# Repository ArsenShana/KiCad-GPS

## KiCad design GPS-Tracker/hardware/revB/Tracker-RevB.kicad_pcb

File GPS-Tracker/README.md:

# GPS Tracker — демонстрационный прототип

Открыть симуляцию: `python3 server.py`, затем http://127.0.0.1:8765 . Презентация: http://127.0.0.1:8765/presentation.html .

Сборка ядра на macOS: `clang++ -std=c++17 -dynamiclib firmware/tracker.cpp -o firmware/libtracker.dylib`.
Проверка: `python3 firmware/test_core.py`.

KiCad: hardware/GPS-Tracker.kicad_pro. Плата — 70 × 45 мм, блоковая компоновка с условными габаритами модулей. Отсутствуют электрические соединения и реальные посадочные места; изготовление по этим файлам недопустимо. Схема — функциональная, а не электрическая.

Результат: работающая локальная симуляция исполняет C++ ядро; 3D модель компоновки, схема обмена, протокол, презентация. Не реализованы физические UART/BLE/LTE драйверы, загрузочный образ, телефонное приложение и production сервер. Локальный сервер обслуживает симуляцию, не является сервером приёма реальных устройств. Модель не оценивает RF, точность GPS, энергопотребление или срок работы батареи.

До выпуска: согласовать операторов/страны, наличие LTE-M/NB-IoT, GNSS выбранного варианта BG95, eUICC и профили оператора, размеры, аккумулятор и срок работы, сервер и приложение Android/iOS. eSIM не создаёт покрытие; телефон помогает только при собственном интернете. См. docs/architecture.md.

## Ревизия B

Улучшенный инженерный черновик: hardware/revB/Tracker-RevB.kicad_pro. Конкретные компоненты, именованные цепи и PCB без трассировки. См. hardware/revB/review.md, BOM.csv, ERC.json и DRC.json. Ревизия не готова к производству.

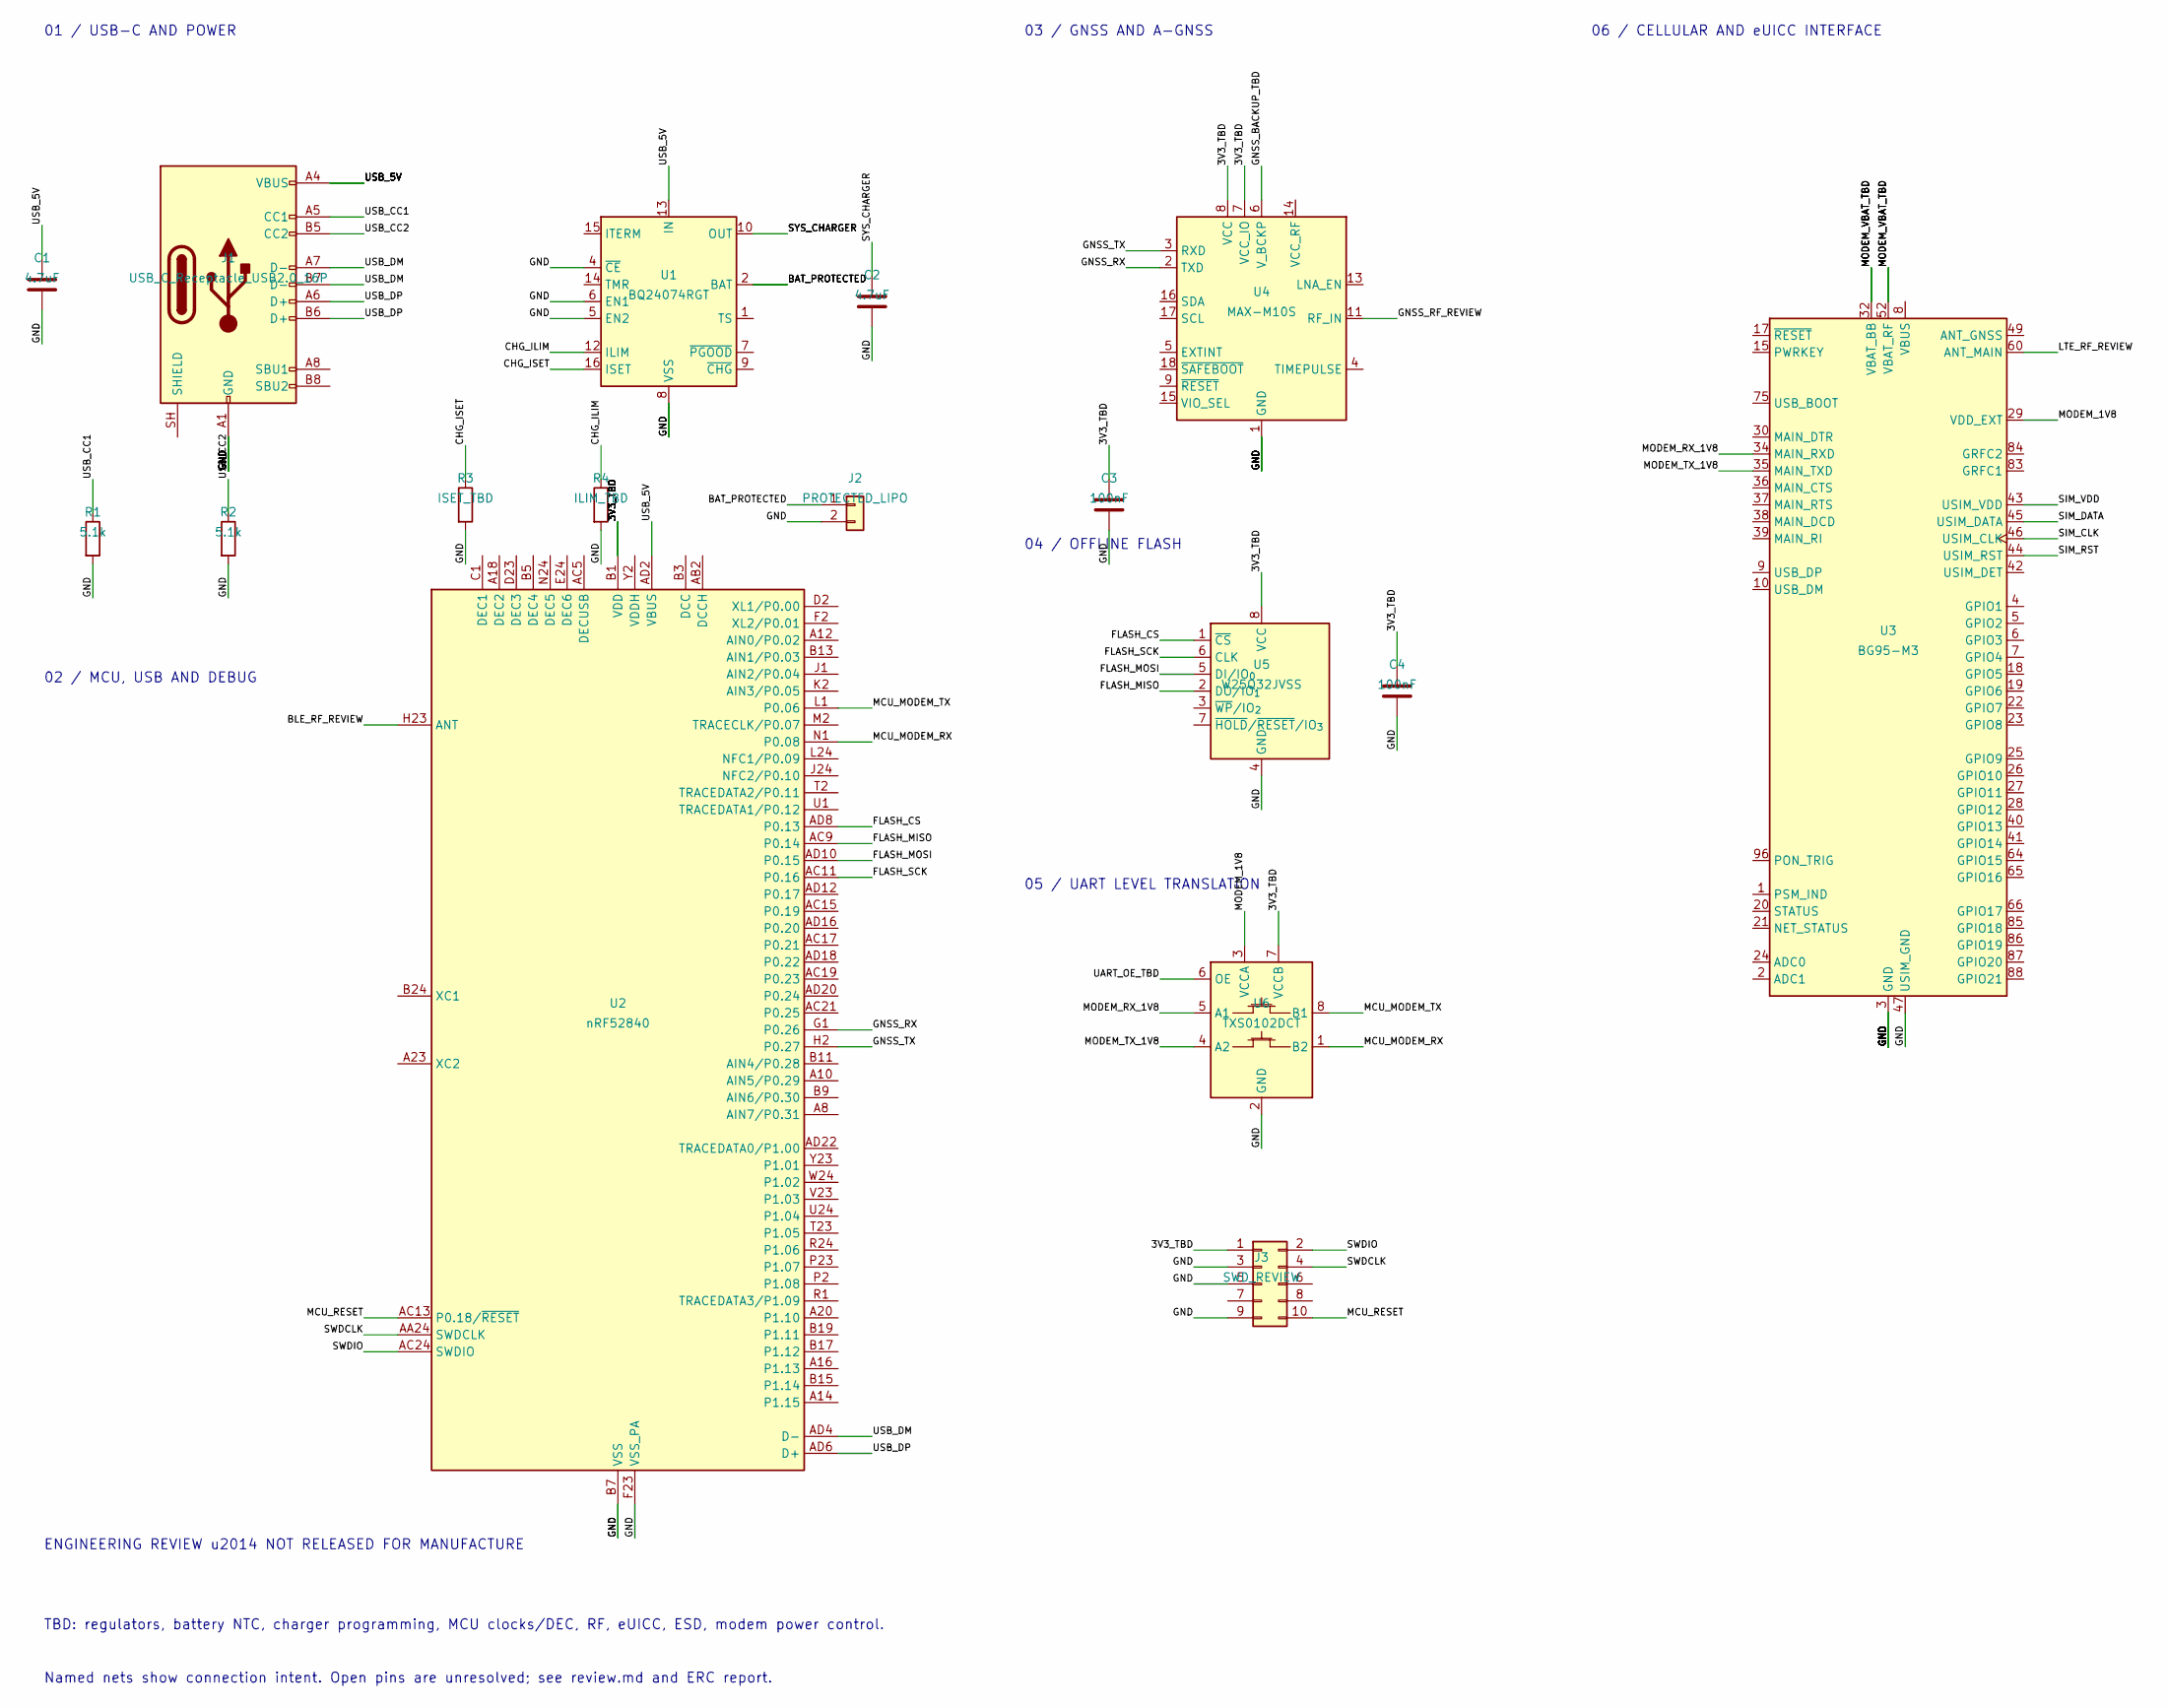
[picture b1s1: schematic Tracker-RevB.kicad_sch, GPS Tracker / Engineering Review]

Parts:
C1, C2: 4.7uF; C_0603_1608Metric
C3, C4: 100nF; C_0603_1608Metric
J1: USB_C_Receptacle_USB2.0_16P; USB_C_Receptacle_GCT_USB4105-xx-A_16P_TopMnt_Horizontal
J2: PROTECTED_LIPO; JST_PH_B2B-PH-K_1x02_P2.00mm_Vertical
J3: SWD_REVIEW; PinHeader_2x05_P1.27mm_Vertical
R1, R2: 5.1k; R_0603_1608Metric
R3: ISET_TBD; R_0603_1608Metric
R4: ILIM_TBD; R_0603_1608Metric
U1: BQ24074RGT; VQFN-16-1EP_3x3mm_P0.5mm_EP1.6x1.6mm
U2: nRF52840; Nordic_AQFN-73-1EP_7x7mm_P0.5mm
U3: BG95-M3; Quectel_BG95
U4: MAX-M10S; ublox_MAX
U5: W25Q32JVSS; SOIC-8_5.3x5.3mm_P1.27mm
U6: TXS0102DCT; SSOP-8_2.95x2.8mm_P0.65mm

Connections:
/3V3_TBD: C3.1, C4.1, J3.1, U2.A22 (VDD), U2.AD14 (VDD), U2.AD23 (VDD), U2.B1 (VDD), U2.W1 (VDD), U4.7 (VCC_IO), U4.8 (VCC), U5.8 (VCC), U6.7 (VCCB)
/BAT_PROTECTED: J2.1, U1.2 (BAT), U1.3 (BAT)
/BLE_RF_REVIEW: U2.H23 (ANT)
/CHG_ILIM: R4.1, U1.12 (ILIM)
/CHG_ISET: R3.1, U1.16 (ISET)
/FLASH_CS: U2.AD8 (P0.13), U5.1 (~CS)
/FLASH_MISO: U2.AC9 (P0.14), U5.2 (DO/IO_{1})
/FLASH_MOSI: U2.AD10 (P0.15), U5.5 (DI/IO_{0})
/FLASH_SCK: U2.AC11 (P0.16), U5.6 (CLK)
/GND: C1.2, C2.2, C3.2, C4.2, J1.A1 (GND), J1.A12 (GND), J1.B1 (GND), J1.B12 (GND), J2.2, J3.3, J3.5, J3.9, R1.2, R2.2, R3.2, R4.2, U1.4 (~CE), U1.5 (EN2), U1.6 (EN1), U1.8 (VSS), U1.17 (VSS), U2.B7 (VSS), U2.EP (VSS), U2.F23 (VSS_PA), U3.3 (GND), U3.31 (GND), U3.47 (USIM_GND), U3.48 (GND), U3.50 (GND), U3.54 (GND), U3.55 (GND), U3.58 (GND), U3.59 (GND), U3.61 (GND), U3.62 (GND), U3.67 (GND), U3.68 (GND), U3.69 (GND), U3.70 (GND), U3.71 (GND), U3.72 (GND), U3.73 (GND), U3.74 (GND), U3.79 (GND), U3.80 (GND), U3.81 (GND), U3.82 (GND), U3.89 (GND), U3.90 (GND), U3.91 (GND), U3.100 (GND), U3.101 (GND), U3.102 (GND), U4.1 (GND), U4.10 (GND), U4.12 (GND), U5.4 (GND), U6.2 (GND)
/GNSS_BACKUP_TBD: U4.6 (V_BCKP)
/GNSS_RF_REVIEW: U4.11 (RF_IN)
/GNSS_RX: U2.G1 (P0.26), U4.2 (TXD)
/GNSS_TX: U2.H2 (P0.27), U4.3 (RXD)
/LTE_RF_REVIEW: U3.60 (ANT_MAIN)
/MCU_MODEM_RX: U2.N1 (P0.08), U6.1 (B2)
/MCU_MODEM_TX: U2.L1 (P0.06), U6.8 (B1)
/MCU_RESET: J3.10, U2.AC13 (P0.18/~RESET)
/MODEM_1V8: U3.29 (VDD_EXT), U6.3 (VCCA)
/MODEM_RX_1V8: U3.34 (MAIN_RXD), U6.5 (A1)
/MODEM_TX_1V8: U3.35 (MAIN_TXD), U6.4 (A2)
/MODEM_VBAT_TBD: U3.32 (VBAT_BB), U3.33 (VBAT_BB), U3.52 (VBAT_RF), U3.53 (VBAT_RF)
/SIM_CLK: U3.46 (USIM_CLK)
/SIM_DATA: U3.45 (USIM_DATA)
/SIM_RST: U3.44 (USIM_RST)
/SIM_VDD: U3.43 (USIM_VDD)
/SWDCLK: J3.4, U2.AA24 (SWDCLK)
/SWDIO: J3.2, U2.AC24 (SWDIO)
/SYS_CHARGER: C2.1, U1.10 (OUT), U1.11 (OUT)
/UART_OE_TBD: U6.6 (OE)
/USB_5V: C1.1, J1.A4 (VBUS), J1.A9 (VBUS), J1.B4 (VBUS), J1.B9 (VBUS), U1.13 (IN), U2.AD2 (VBUS)
/USB_CC1: J1.A5 (CC1), R1.1
/USB_CC2: J1.B5 (CC2), R2.1
/USB_DM: J1.A7 (D-), J1.B7 (D-), U2.AD4 (D-)
/USB_DP: J1.A6 (D+), J1.B6 (D+), U2.AD6 (D+)

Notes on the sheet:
01 / USB-C AND POWER
02 / MCU, USB AND DEBUG
03 / GNSS AND A-GNSS
04 / OFFLINE FLASH
05 / UART LEVEL TRANSLATION
06 / CELLULAR AND eUICC INTERFACE
ENGINEERING REVIEW u2014 NOT RELEASED FOR MANUFACTURE
TBD: regulators, battery NTC, charger programming, MCU clocks/DEC, RF, eUICC, ESD, modem power control.
Named nets show connection intent. Open pins are unresolved; see review.md and ERC report.

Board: 4 copper layers, 21 parts (0 on the bottom side), 26 nets, no tracks yet.

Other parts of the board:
H1, H2, H3, H4: MountingHole_2.2mm_M2

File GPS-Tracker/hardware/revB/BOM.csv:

Reference,Value,Footprint,Status
J1,USB_C_Receptacle_USB2.0_16P,Connector_USB:USB_C_Receptacle_GCT_USB4105-xx-A_16P_TopMnt_Horizontal,DRAFT: verify datasheet and assembly
U1,BQ24074RGT,Package_DFN_QFN:VQFN-16-1EP_3x3mm_P0.5mm_EP1.6x1.6mm,DRAFT: verify datasheet and assembly
U2,nRF52840,Package_DFN_QFN:Nordic_AQFN-73-1EP_7x7mm_P0.5mm,DRAFT: verify datasheet and assembly
U3,BG95-M3,RF_GSM:Quectel_BG95,DRAFT: verify datasheet and assembly
U4,MAX-M10S,RF_GPS:ublox_MAX,DRAFT: verify datasheet and assembly
U5,W25Q32JVSS,Package_SO:SOIC-8_5.3x5.3mm_P1.27mm,DRAFT: verify datasheet and assembly
U6,TXS0102DCT,Package_SO:SSOP-8_2.95x2.8mm_P0.65mm,DRAFT: verify datasheet and assembly
R1,5.1k,Resistor_SMD:R_0603_1608Metric,DRAFT: verify datasheet and assembly
R2,5.1k,Resistor_SMD:R_0603_1608Metric,DRAFT: verify datasheet and assembly
R3,ISET_TBD,Resistor_SMD:R_0603_1608Metric,DRAFT: verify datasheet and assembly
R4,ILIM_TBD,Resistor_SMD:R_0603_1608Metric,DRAFT: verify datasheet and assembly
C1,4.7uF,Capacitor_SMD:C_0603_1608Metric,DRAFT: verify datasheet and assembly
C2,4.7uF,Capacitor_SMD:C_0603_1608Metric,DRAFT: verify datasheet and assembly
C3,100nF,Capacitor_SMD:C_0603_1608Metric,DRAFT: verify datasheet and assembly
C4,100nF,Capacitor_SMD:C_0603_1608Metric,DRAFT: verify datasheet and assembly
J2,PROTECTED_LIPO,Connector_JST:JST_PH_B2B-PH-K_1x02_P2.00mm_Vertical,DRAFT: verify datasheet and assembly
J3,SWD_REVIEW,Connector_PinHeader_1.27mm:PinHeader_2x05_P1.27mm_Vertical,DRAFT: verify datasheet and assembly
